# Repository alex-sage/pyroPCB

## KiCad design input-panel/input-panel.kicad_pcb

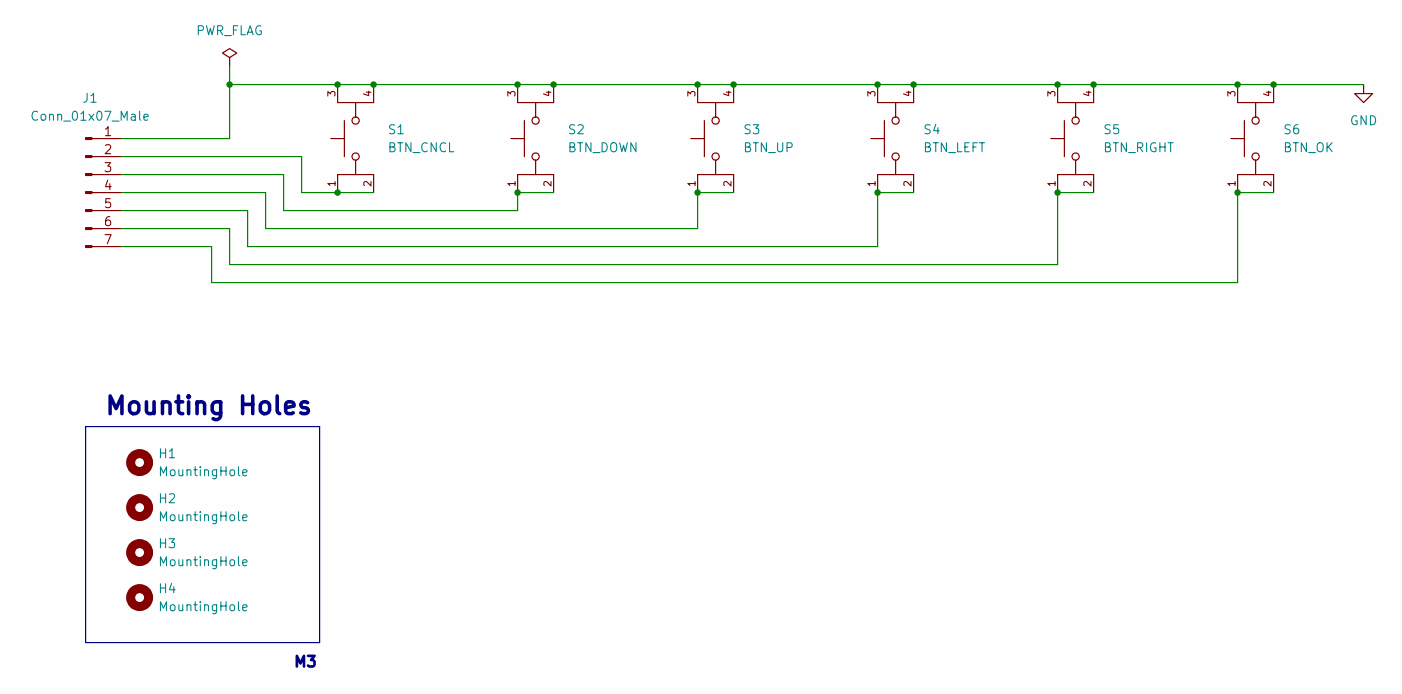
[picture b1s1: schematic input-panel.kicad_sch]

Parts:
H1, H2, H3, H4: MountingHole; MountingHole_3.2mm_M3
J1: Conn_01x07_Male; PinHeader_1x07_P2.54mm_Vertical
S1: BTN_CNCL; SW_TL1105DF160Q; PARTREV A
S2: BTN_DOWN; SW_TL1105DF160Q; PARTREV A
S3: BTN_UP; SW_TL1105DF160Q; PARTREV A
S4: BTN_LEFT; SW_TL1105DF160Q; PARTREV A
S5: BTN_RIGHT; SW_TL1105DF160Q; PARTREV A
S6: BTN_OK; SW_TL1105DF160Q; PARTREV A

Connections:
GND: J1.1, S1.3, S1.4, S2.3, S2.4, S3.3, S3.4, S4.3, S4.4, S5.3, S5.4, S6.3, S6.4
unnamed: J1.2, S1.1, S1.2
unnamed: J1.3, S2.1, S2.2
unnamed: J1.4, S3.1, S3.2
unnamed: J1.5, S4.1, S4.2
unnamed: J1.6, S5.1, S5.2
unnamed: J1.7, S6.1, S6.2

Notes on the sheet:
Mounting Holes

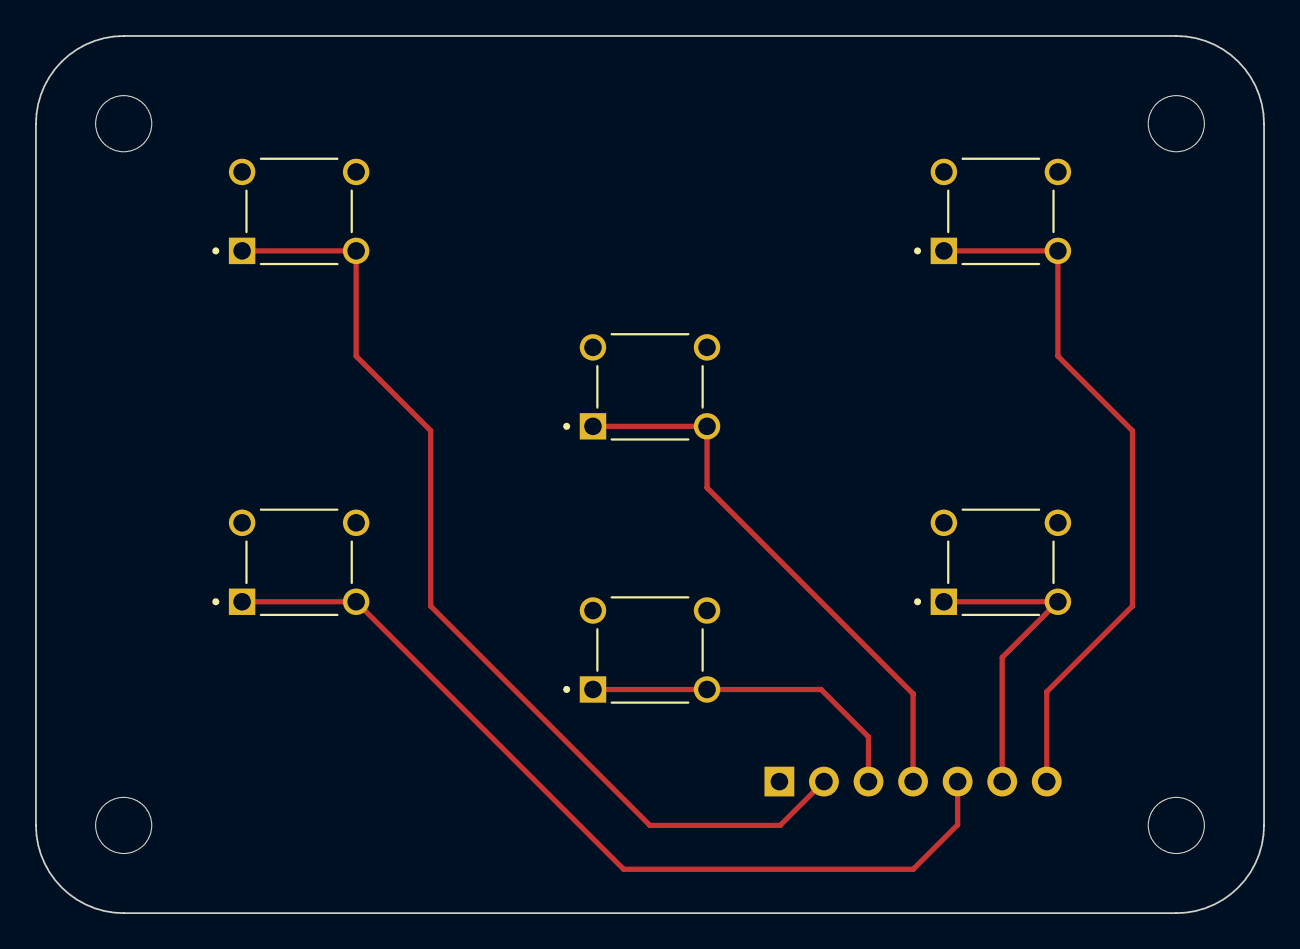
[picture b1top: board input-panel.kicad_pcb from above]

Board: 2 copper layers, 70.0 x 50.0 mm, 11 parts (1 on the bottom side), 7 nets.

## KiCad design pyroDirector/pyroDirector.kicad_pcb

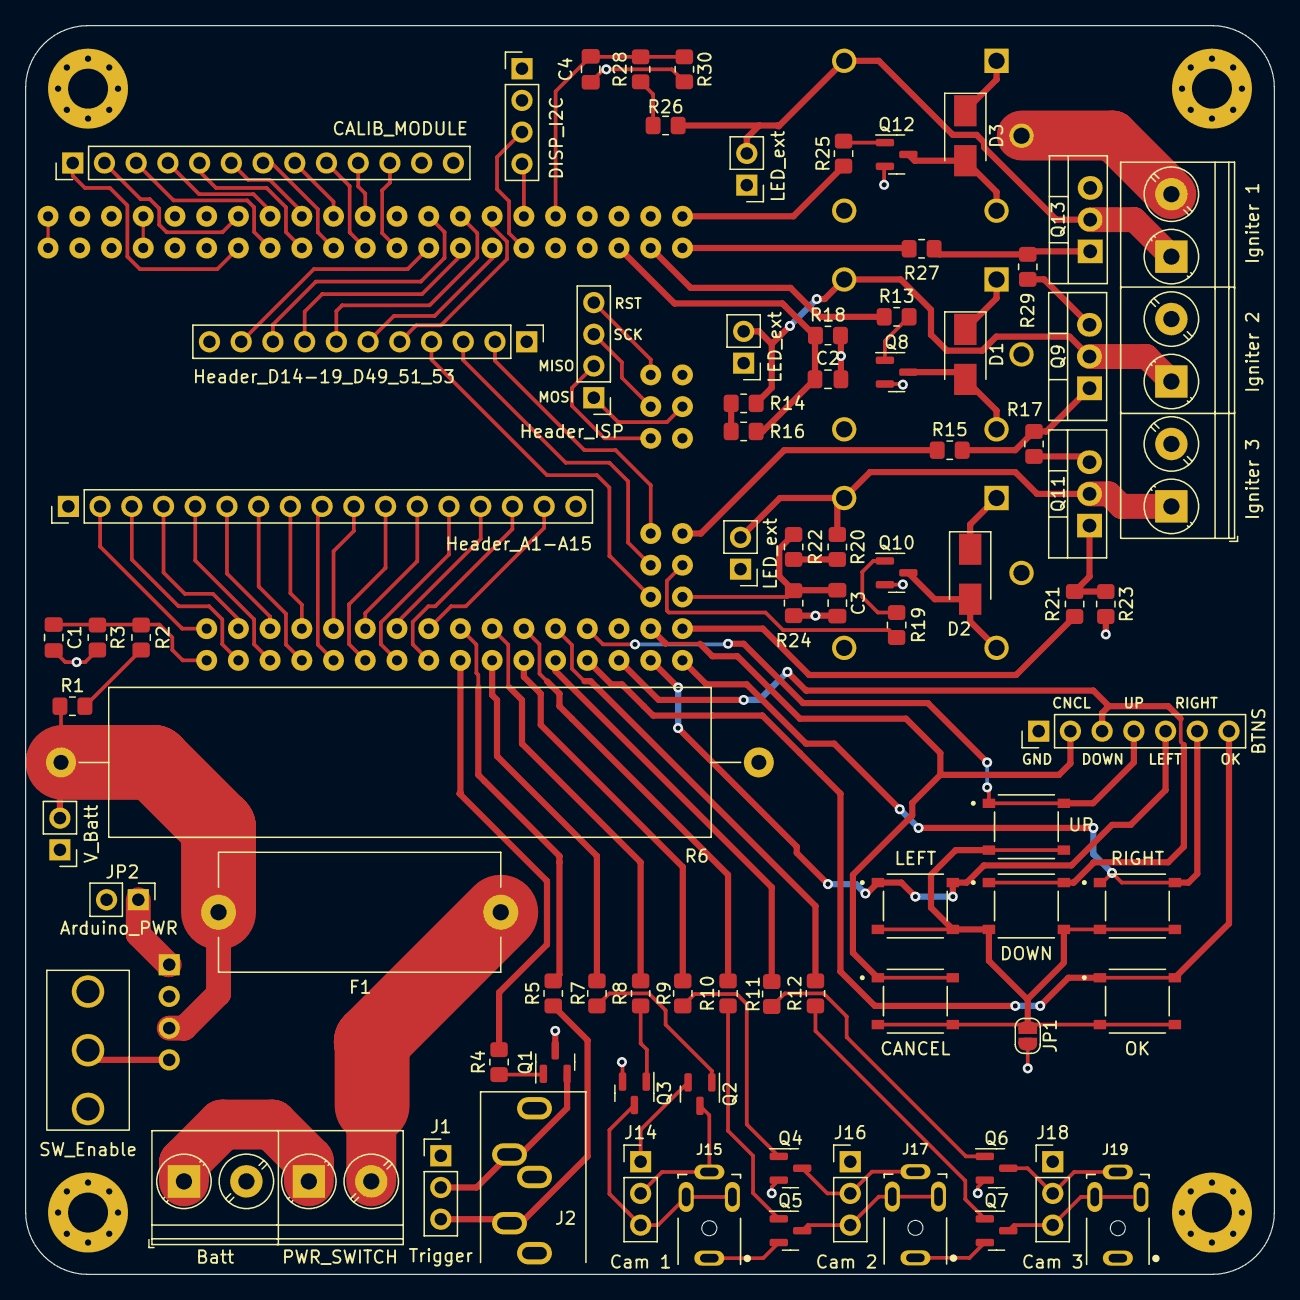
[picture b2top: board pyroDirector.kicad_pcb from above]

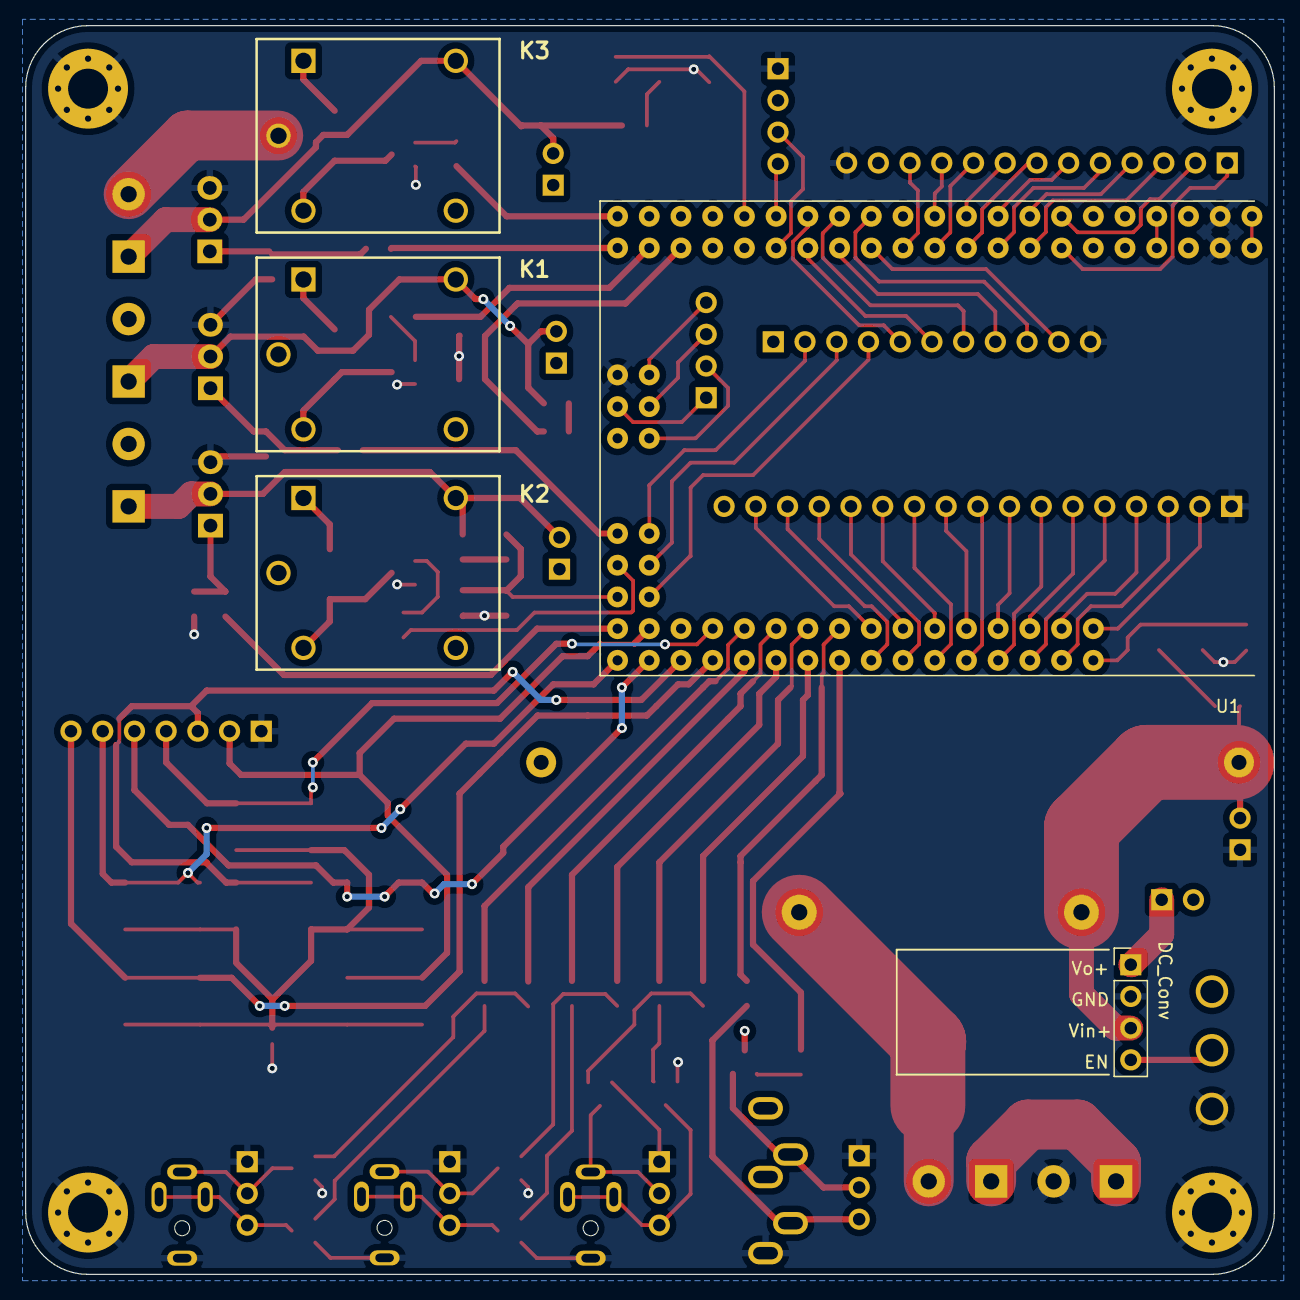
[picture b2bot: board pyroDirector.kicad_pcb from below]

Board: 4 copper layers, 100.0 x 100.0 mm, 92 parts (5 on the bottom side), 108 nets.

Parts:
C1, C2, C3, C4: 100n; C_0805_2012Metric_Pad1.18x1.45mm_HandSolder
D1, D2, D3: M7; D_SMA
F1: Fuse; Fuseholder_Cylinder-5x20mm_Wuerth_WR-FSH
H1, H2, H3, H4: MountingHole; MountingHole_3.2mm_M3_Pad_Via
J1, J14, J16, J18: Conn_01x03_Male; PinHeader_1x03_P2.54mm_Vertical
J2: AudioJack3.5mm; Jack_3.5mm_CUI_SJ1-3535NG_Horizontal
J3: Header_A1-A15; PinHeader_1x17_P2.54mm_Vertical
J4: Header_D14-19_D49_51_53; PinHeader_1x11_P2.54mm_Vertical
J6: V_Batt; PinHeader_1x02_P2.54mm_Vertical
J7: Header_ISP; PinHeader_1x04_P2.54mm_Vertical
J8: PWR_SWITCH; TerminalBlock_Phoenix_PT-1,5-2-5.0-H_1x02_P5.00mm_Horizontal
J9: Batt; TerminalBlock_Phoenix_PT-1,5-2-5.0-H_1x02_P5.00mm_Horizontal
J10: BTNS; PinHeader_1x07_P2.54mm_Vertical
J11: DC_Conv; PinHeader_1x04_P2.54mm_Vertical
J12: CALIB_MODULE; PinHeader_1x13_P2.54mm_Vertical
J13: DISP_I2C; PinHeader_1x04_P2.54mm_Vertical
J15, J17, J19: SJ1-2503A; CUI_SJ1-2503A
J20, J22, J24: LED_ext; PinHeader_1x02_P2.54mm_Vertical
J21, J23, J25: Screw_Terminal_01x02; TerminalBlock_Phoenix_PT-1,5-2-5.0-H_1x02_P5.00mm_Horizontal
JP1: Enable_PCB_Buttons; SolderJumper-2_P1.3mm_Open_RoundedPad1.0x1.5mm
JP2: Arduino_PWR; PinHeader_1x02_P2.54mm_Vertical
K1, K2, K3: PR12-5V-360-1C
Q1, Q2, Q3, Q4, Q5, Q6, Q7, Q8, Q10, Q12: MMBT2222A 1P; SOT-23
Q9, Q11, Q13: IRLB8721PbF; TO-220-3_Vertical
R1, R2, R3, R14, R16, R18, R20, R22, R24, R26, R28, R30: 1M; R_0805_2012Metric_Pad1.20x1.40mm_HandSolder
R4, R5, R7, R8, R9, R10, R11, R12, R13, R19, R25: 4k7; R_0805_2012Metric_Pad1.20x1.40mm_HandSolder
R6: 1R; R_Axial_Power_L48.0mm_W10mm_P55.88mm
R15, R21, R27: 100R; R_0805_2012Metric_Pad1.20x1.40mm_HandSolder
R17, R23, R29: 47k; R_0805_2012Metric_Pad1.20x1.40mm_HandSolder
S1: PCB_Btn_Cncl; SW_TS-1187A-B-A-B
S2: PCB_Btn_-; SW_TS-1187A-B-A-B
S3: PCB_Btn_+; SW_TS-1187A-B-A-B
S4: PCB_Btn_LEFT; SW_TS-1187A-B-A-B
S5: PCB_Btn_RIGHT; SW_TS-1187A-B-A-B
S6: PCB_Btn_OK; SW_TS-1187A-B-A-B
SW1: SW_Enable; Saleforce_T80-S_TS-13_Slide_Switch
U1: MEGA_PRO_ATMEGA2560; MODULE_MEGA_PRO_EMBED_CH340G___ATMEGA2560

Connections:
12V_LTD: J20.1, J22.1, J24.1, K1.NO, K2.NO, K3.NO, R6.2
+5V: D1.1 (K), D2.1 (K), D3.1 (K), J3.17, J4.1, J12.12, J13.2, JP2.2 (B), K1.A1 (Coil_1), K2.A1 (Coil_1), K3.A1 (Coil_1), Q1.3 (C), U1.5V_1 (5V), U1.5V_2 (5V), U1.5V_3 (5V)
+12V: F1.2, J6.2, J11.3, R1.1, R6.1
/A1: J3.2, U1.A1
/A2: J3.3, U1.A2
/A3: J3.4, U1.A3
/A4: J3.5, U1.A4
/A5: J3.6, U1.A5
/A6: J3.7, U1.A6
/A7: J3.8, U1.A7
/A8: J3.9, U1.A8
/A9: J3.10, U1.A9
/A10: J3.11, U1.A10
/A11: J3.12, U1.A11
/A12: J3.13, U1.A12
/A13: J3.14, U1.A13
/A14: J3.15, U1.A14
/A15: J3.16, U1.A15
/BATT_SENSE: C1.1, R2.2, R3.1, U1.A0
/BTN_CNCL: J10.2, S1.A, S1.B, U1.D45
/BTN_DOWN: J10.3, S2.A, S2.B, U1.D42
/BTN_LEFT: J10.5, S4.A, S4.B, U1.D44
/BTN_OK: J10.7, S6.A, S6.B, U1.D40
/BTN_RIGHT: J10.6, S5.A, S5.B, U1.D46
/BTN_UP: J10.4, S3.A, S3.B, U1.D41
/D14: J4.10, U1.D14
/D15: J4.9, U1.D15
/D16: J4.8, U1.D16
/D17: J4.7, U1.D17
/D18: J4.6, U1.D18
/D19: J4.5, U1.D19
/D49: J4.4, U1.D49
/D51: J4.3, U1.D51
/D53: J4.2, U1.D53
/DISP_SCL: J13.4, U1.D21
/DISP_SDA: J13.3, U1.D20
/EN: J11.4, SW1.2 (B)
/FIRE_0: R27.1, U1.D30
/FIRE_1: R15.1, U1.D52
/FIRE_2: R21.1, U1.D47
/LED_1: J12.1, U1.D2
/LED_2: J12.2, U1.D3
/LED_3: J12.3, U1.D4
/LED_4: J12.4, U1.D5
/LED_5: J12.5, U1.D6
/LED_6: J12.6, U1.D7
/LED_7: J12.7, U1.D8
/LED_8: J12.8, U1.D9
/LED_9: J12.9, U1.D10
/LED_10: J12.10, U1.D11
/LED_G: J12.11, U1.D12
/MISO: J7.2, U1.MISO
/MOSI: J7.1, U1.MOSI
/PRE_CAM_0: R7.1, U1.D34
/PRE_CAM_1: R9.1, U1.D36
/PRE_CAM_2: R11.1, U1.D38
/PRIME_0: R25.1, U1.D31
/PRIME_1: R13.1, U1.D28
/PRIME_2: R19.1, U1.D50
/RST: J7.4, U1.RESET
/SCK: J7.3, U1.SCK
/SENSE_0: C4.1, R28.2, R30.1, U1.D23
/SENSE_1: C2.1, R16.2, R18.1, U1.D26
/SENSE_2: C3.1, R22.2, R24.1, U1.D48
/SHUTTER_CAM_0: R8.2, U1.D35
/SHUTTER_CAM_1: R10.2, U1.D37
/SHUTTER_CAM_2: R12.2, U1.D39
/TRIGGER: R5.2, U1.D33
/TRIGGER_LED: R4.2, U1.D32
/VO+: J11.1, JP2.1 (A)
GND: C1.2, C2.2, C3.2, C4.2, H1.1, H2.1, H3.1, H4.1, J1.1, J2.S, J3.1, J4.11, J6.1, J9.2, J10.1, J11.2, J12.13, J13.1, J14.1, J15.1, J16.1, J17.1, J18.1, J19.1, JP1.2 (B), Q2.2 (E), Q3.2 (E), Q4.2 (E), Q5.2 (E), Q6.2 (E), Q7.2 (E), Q8.2 (E), Q9.3 (S), Q10.2 (E), Q11.3 (S), Q12.2 (E), Q13.3 (S), R3.2, R17.2, R18.2, R23.2, R24.2, R29.2, R30.2, SW1.3 (C), U1.GND_1 (GND), U1.GND_2 (GND), U1.GND_3 (GND)
unnamed: D1.2 (A), K1.A2 (Coil_2), Q8.3 (C)
unnamed: D2.2 (A), K2.A2 (Coil_2), Q10.3 (C)
unnamed: D3.2 (A), K3.A2 (Coil_2), Q12.3 (C)
unnamed: F1.1, J8.2
unnamed: J1.2, J2.R, Q1.2 (E)
unnamed: J1.3, J2.T, R5.1
unnamed: J8.1, J9.1
unnamed: J14.2, J15.4, Q2.3 (C)
unnamed: J14.3, J15.2, J15.3, Q3.3 (C)
unnamed: J16.2, J17.4, Q4.3 (C)
unnamed: J16.3, J17.2, J17.3, Q5.3 (C)
unnamed: J18.2, J19.4, Q6.3 (C)
unnamed: J18.3, J19.2, J19.3, Q7.3 (C)
unnamed: J20.2, J21.1, K1.NC, Q9.2 (D), R14.1
unnamed: J21.2, K1.COM
unnamed: J22.2, J23.1, K2.NC, Q11.2 (D), R20.1
unnamed: J23.2, K2.COM
unnamed: J24.2, J25.1, K3.NC, Q13.2 (D), R26.1
unnamed: J25.2, K3.COM
unnamed: JP1.1 (A), S1.C, S1.D, S2.C, S2.D, S3.C, S3.D, S4.C, S4.D, S5.C, S5.D, S6.C, S6.D
unnamed: Q1.1 (B), R4.1
unnamed: Q2.1 (B), R7.2
unnamed: Q3.1 (B), R8.1
unnamed: Q4.1 (B), R9.2
unnamed: Q5.1 (B), R10.1
unnamed: Q6.1 (B), R11.2
unnamed: Q7.1 (B), R12.1
unnamed: Q8.1 (B), R13.2
unnamed: Q9.1 (G), R15.2, R17.1
unnamed: Q10.1 (B), R19.2
unnamed: Q11.1 (G), R21.2, R23.1
unnamed: Q12.1 (B), R25.2
unnamed: Q13.1 (G), R27.2, R29.1
unnamed: R1.2, R2.1
unnamed: R14.2, R16.1
unnamed: R20.2, R22.1
unnamed: R26.2, R28.1

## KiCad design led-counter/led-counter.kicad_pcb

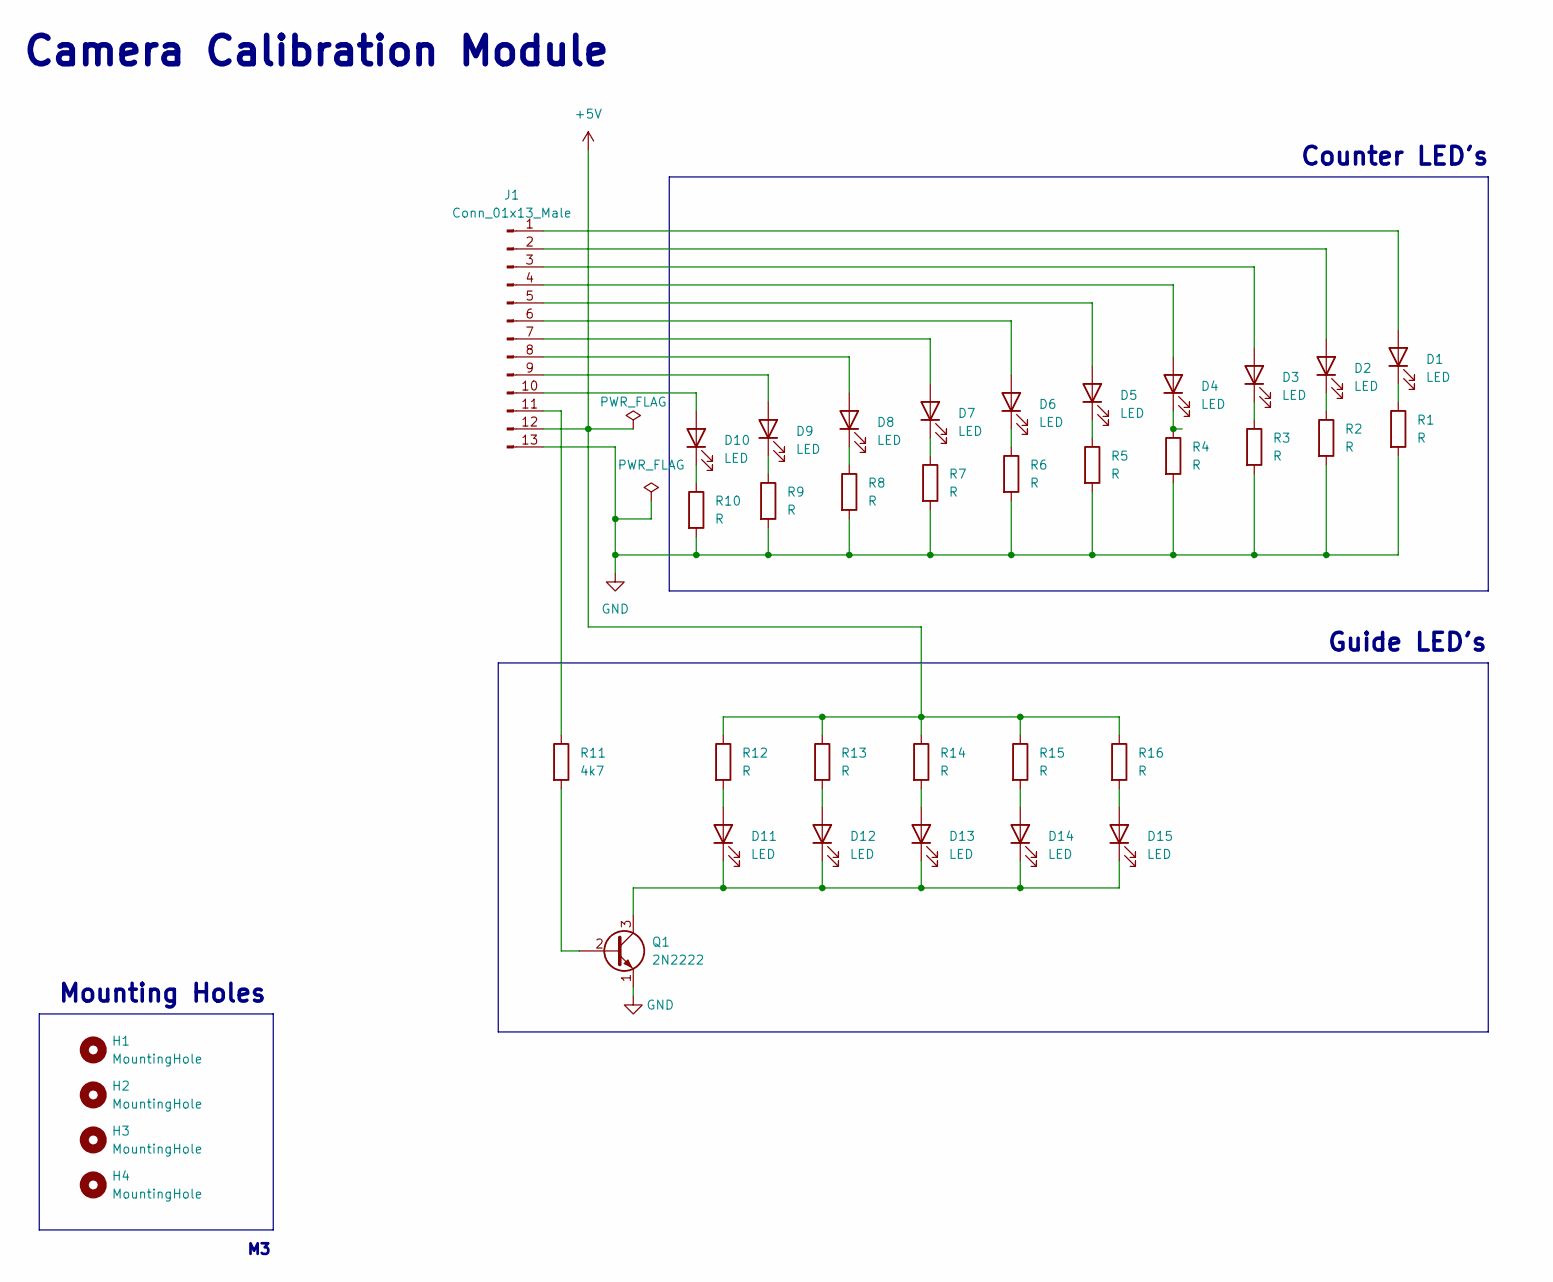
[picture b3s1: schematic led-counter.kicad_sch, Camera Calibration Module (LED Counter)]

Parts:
D1, D2, D3, D4, D5, D6, D7, D8, D9, D10, D11, D12, D13, D14, D15: LED; LED_D5.0mm
H1, H2, H3, H4: MountingHole; MountingHole_3.2mm_M3
J1: Conn_01x13_Male; PinHeader_1x13_P2.54mm_Vertical
Q1: 2N2222; TO-92
R1, R2, R3, R4, R5, R6, R7, R8, R9, R10, R12, R13, R14, R15, R16: R; R_Axial_DIN0204_L3.6mm_D1.6mm_P7.62mm_Horizontal
R11: 4k7; R_Axial_DIN0204_L3.6mm_D1.6mm_P7.62mm_Horizontal

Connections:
+5V: J1.12, R12.1, R13.1, R14.1, R15.1, R16.1
GND: J1.13, Q1.1 (E), R1.2, R2.2, R3.2, R4.2, R5.2, R6.2, R7.2, R8.2, R9.2, R10.2
unnamed: D1.1 (K), R1.1
unnamed: D1.2 (A), J1.1
unnamed: D2.1 (K), R2.1
unnamed: D2.2 (A), J1.2
unnamed: D3.1 (K), R3.1
unnamed: D3.2 (A), J1.3
unnamed: D4.1 (K), R4.1
unnamed: D4.2 (A), J1.4
unnamed: D5.1 (K), R5.1
unnamed: D5.2 (A), J1.5
unnamed: D6.1 (K), R6.1
unnamed: D6.2 (A), J1.6
unnamed: D7.1 (K), R7.1
unnamed: D7.2 (A), J1.7
unnamed: D8.1 (K), R8.1
unnamed: D8.2 (A), J1.8
unnamed: D9.1 (K), R9.1
unnamed: D9.2 (A), J1.9
unnamed: D10.1 (K), R10.1
unnamed: D10.2 (A), J1.10
unnamed: D11.1 (K), D12.1 (K), D13.1 (K), D14.1 (K), D15.1 (K), Q1.3 (C)
unnamed: D11.2 (A), R12.2
unnamed: D12.2 (A), R13.2
unnamed: D13.2 (A), R14.2
unnamed: D14.2 (A), R15.2
unnamed: D15.2 (A), R16.2
unnamed: J1.11, R11.1
unnamed: Q1.2 (B), R11.2

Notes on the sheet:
Guide LED's
Camera Calibration Module
Mounting Holes
Counter LED's

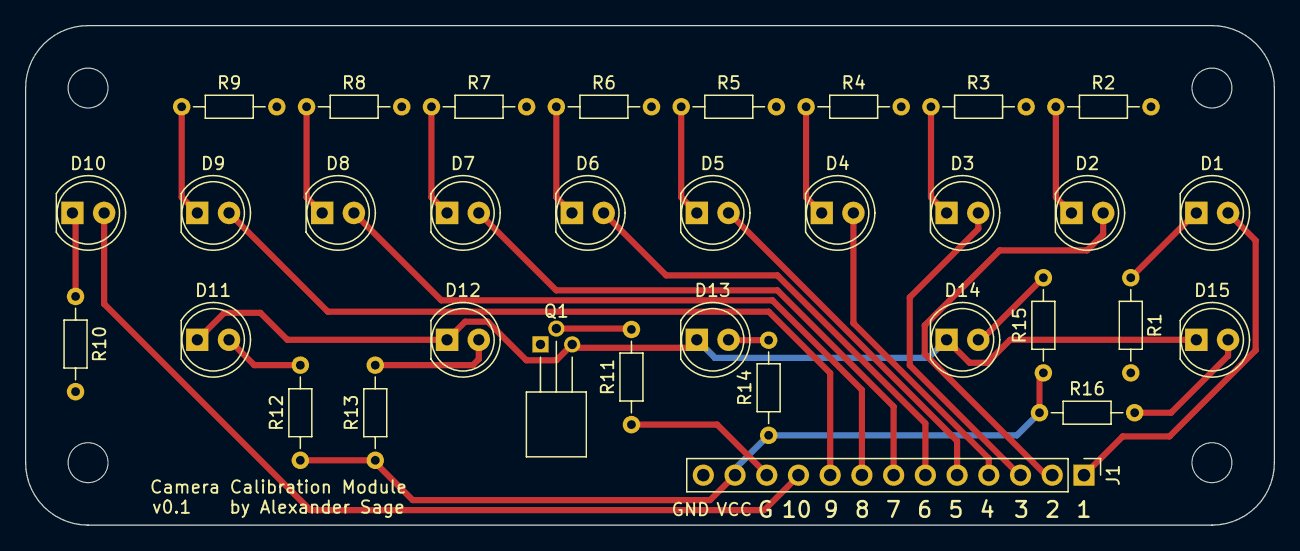
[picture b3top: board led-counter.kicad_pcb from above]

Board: 2 copper layers, 100.0 x 40.0 mm, 37 parts (0 on the bottom side), 30 nets.

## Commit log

2023-01-26 initial commit for main PCB
2023-01-26 initial commit for LED counter
2023-01-26 add datasheets
2023-01-30 Added jacks and PCB switch
2023-02-05 first component placement, trigger header is missing!
2023-02-10 placement improvements, added missing header -->should we use handsolder pads?
2023-02-11 placement & 3-D models complete
2023-02-12 layout in progress
2023-02-25 final design
2023-02-25 Manufactured 2021-02-25
2023-02-28 added input panel project
2023-03-01 re-designed input panel PCB
2024-01-21 added backup directories to gitignore
2024-01-21 replaced trigger transistor with PNP variant
